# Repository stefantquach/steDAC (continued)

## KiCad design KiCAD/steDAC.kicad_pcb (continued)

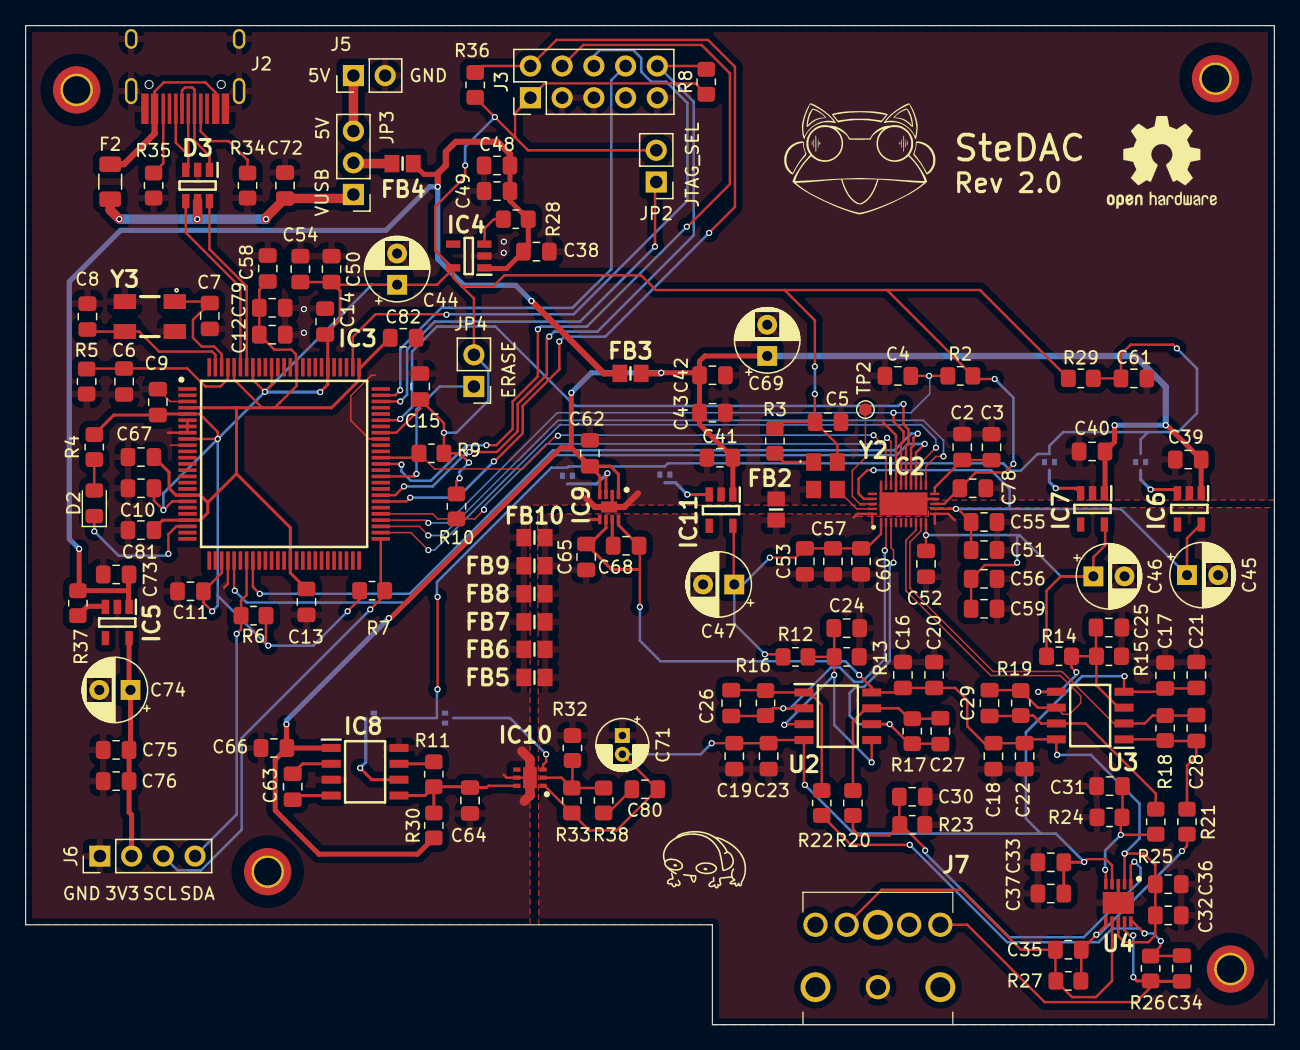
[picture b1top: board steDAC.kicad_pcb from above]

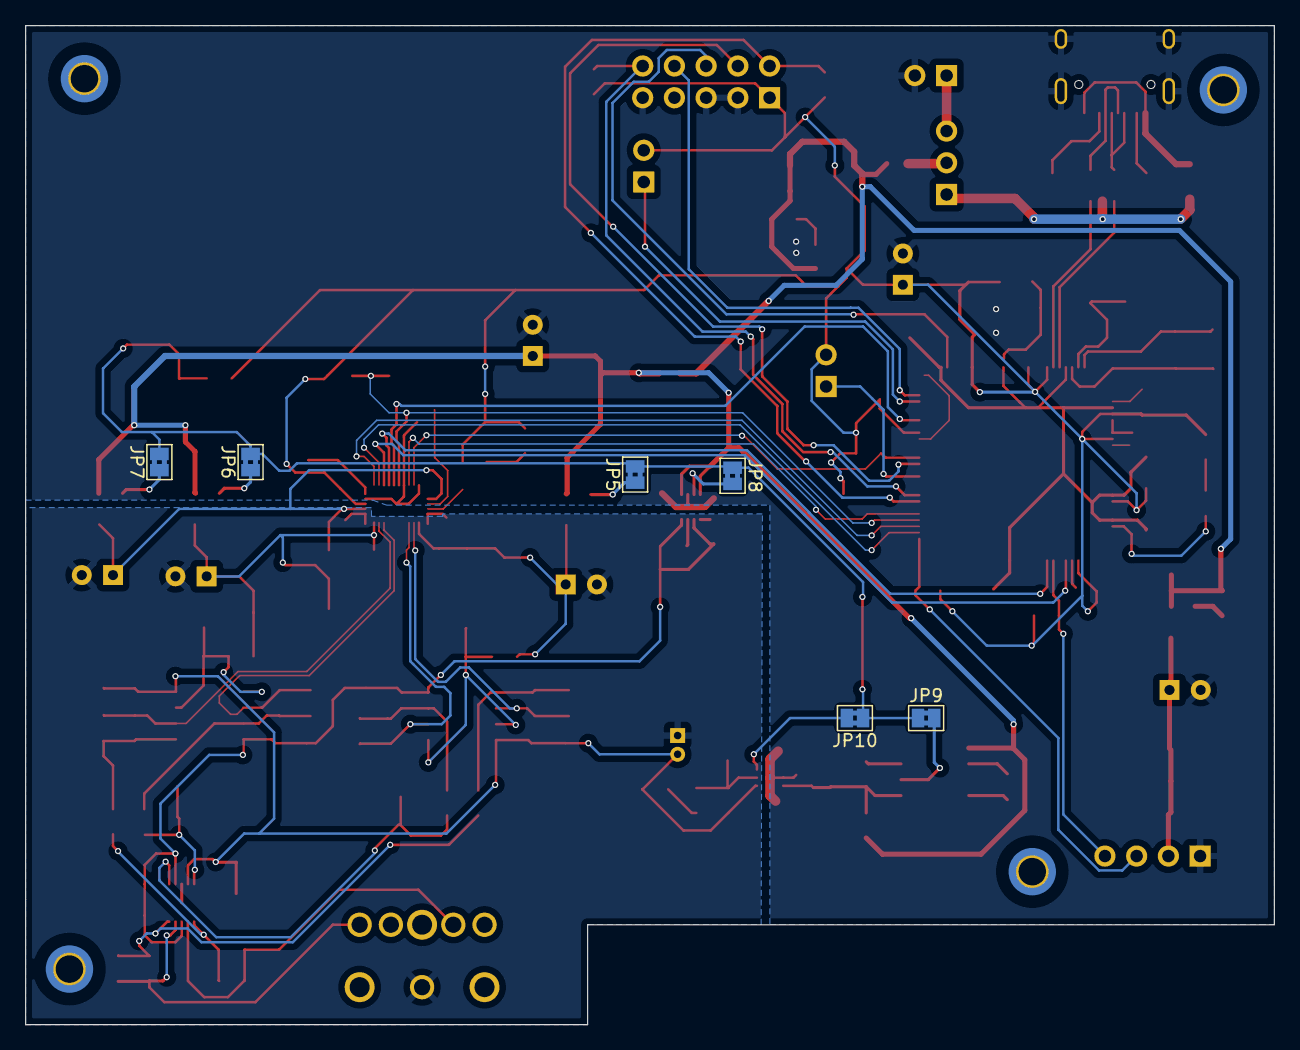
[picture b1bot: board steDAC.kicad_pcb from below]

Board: 2 copper layers, 100.0 x 80.0 mm, 161 parts (6 on the bottom side), 80 nets.

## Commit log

2022-01-11 Initial commit of AK4493 connections
2022-02-07 Adding Initial MCU configuration
2022-02-12 Adding ES9038 parts
2022-02-14 Adding ES9038q2m configuration
2022-02-20 WIP output stage
2022-02-27 Adding values to output stage
2022-03-03 Redoing power stage and changing output stage accordingly
2022-03-05 Finishing MCU interface. Adding connectors
2022-03-06 Adding MCU LED
2022-04-10 Finishing Schematic. Fixed ERC errors
2022-04-10 Adding footprints
2022-04-24 Adding footprints. WIP PCB, finished routing, no ground planes yet
2022-04-24 Adding some missing nets
2022-04-24 Moving some traces around
2022-04-24 Updating pcb design
2022-04-25 Finishing routing and ground planes
2022-04-25 Updating PCB schematic DRC
2022-05-09 Adding part numbers for passives
2022-05-09 Adding more part numbers. WIP verifying part numbers
2022-05-11 Adding logos and finish up bom
2022-05-11 Adding readme
2022-05-11 Moving USB closer to edge. Adding silkscreen text for ERASE and JTAG_SEL. Updating README
2022-05-12 Fixing some via sizes
2022-05-12 Updating stuff
2022-05-14 Changing negative rail power supply
2022-05-14 Trace edits
2022-05-18 Reorganzing
2022-05-18 Adding pdf version of schematic
2022-05-19 Adding pcb pdfs
2022-05-20 Adding gerbers
2022-05-31 Updating BOM generator script
2022-06-07 [REV1.0.1] Rerouting some traces in the output stage. Adding rev1.0.1 gerbers
2022-07-02 REV 1.0.1 does not work. Updating BOM IDs.
2022-07-03 Fixing 3.3V being fed to VDDCORE. Swaping 3.3V LDOs to onsemi ones with higher output current
2022-07-04 Updating gerbers, schematics and BOM for Rev 1.1.0
2022-07-17 Adding stuff for rev 2.0
2022-07-19 Adding updated schematic PDF and BOM
2022-11-11 Committing interim changes
